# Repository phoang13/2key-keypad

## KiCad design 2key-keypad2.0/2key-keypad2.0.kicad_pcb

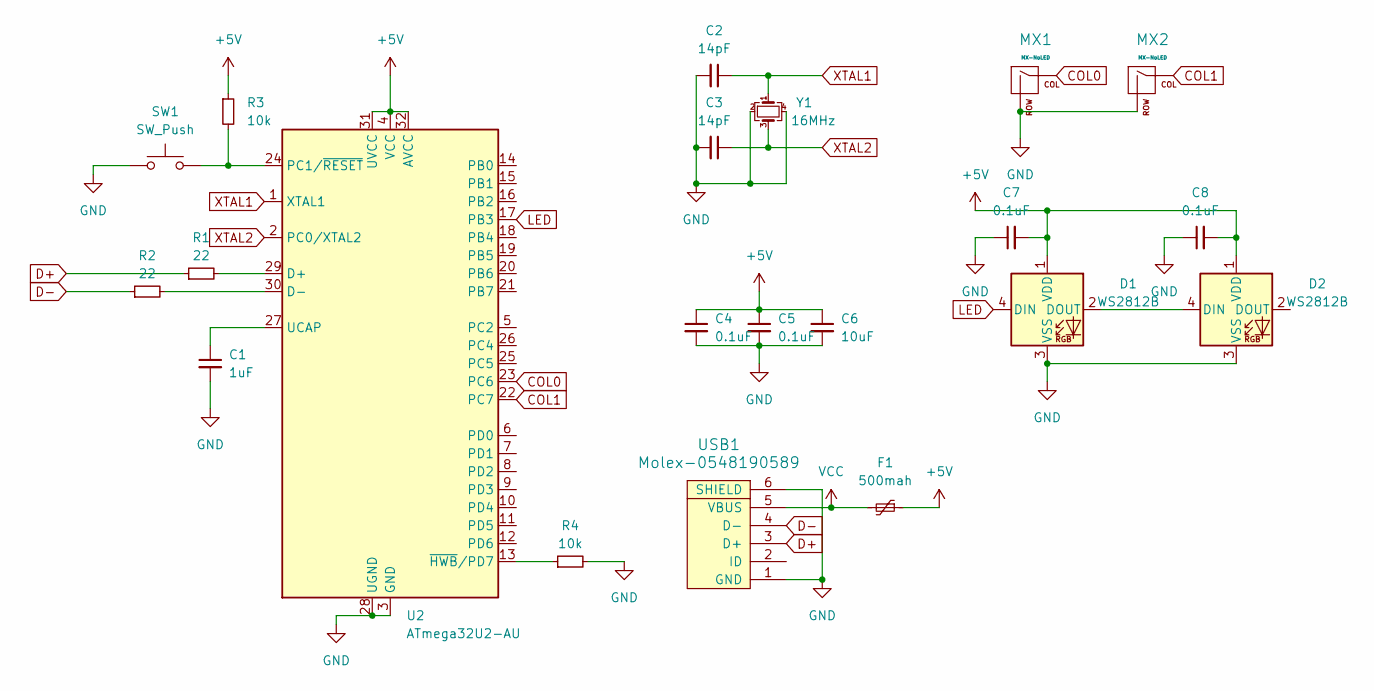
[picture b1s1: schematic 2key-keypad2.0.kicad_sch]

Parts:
C1: 1uF; C_0805_2012Metric_Pad1.18x1.45mm_HandSolder
C2, C3: 14pF; C_0805_2012Metric_Pad1.18x1.45mm_HandSolder
C4, C5, C7, C8: 0.1uF; C_0805_2012Metric_Pad1.18x1.45mm_HandSolder
C6: 10uF; C_0805_2012Metric_Pad1.18x1.45mm_HandSolder
D1, D2: WS2812B; LED_WS2812B_PLCC4_5.0x5.0mm_P3.2mm
F1: 500mah; Fuse_1206_3216Metric_Pad1.42x1.75mm_HandSolder
MX1, MX2: MX-NoLED; MXOnly-1U-Hotswap
R1, R2: 22; R_0805_2012Metric_Pad1.20x1.40mm_HandSolder
R3, R4: 10k; R_0805_2012Metric_Pad1.20x1.40mm_HandSolder
SW1: SW_Push; SKQGADE010
U2: ATmega32U2-AU; TQFP-32_7x7mm_P0.8mm
USB1: Molex-0548190589
Y1: 16MHz; Crystal_SMD_3225-4Pin_3.2x2.5mm_HandSoldering

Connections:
+5V: C4.1, C5.1, C6.1, C7.2, C8.2, D1.1 (VDD), D2.1 (VDD), F1.1, R3.1, U2.4 (VCC), U2.31 (UVCC), U2.32 (AVCC)
COL0: MX1.1 (COL), U2.23 (PC6)
COL1: MX2.1 (COL), U2.22 (PC7)
D+: R1.1, USB1.3 (D+)
D-: R2.1, USB1.4 (D-)
GND: C1.2, C2.2, C3.2, C4.2, C5.2, C6.2, C7.1, C8.1, D1.3 (VSS), D2.3 (VSS), MX1.2 (ROW), MX2.2 (ROW), R4.2, SW1.1, U2.3 (GND), U2.28 (UGND), USB1.1 (GND), USB1.6 (SHIELD), Y1.2, Y1.4
LED: D1.4 (DIN), U2.17 (PB3)
unnamed: D1.2 (DOUT), D2.4 (DIN)
unnamed: R1.2, U2.29 (D+)
unnamed: R2.2, U2.30 (D-)
unnamed: R3.2, SW1.2, U2.24 (PC1/~RESET)
unnamed: C1.1, U2.27 (UCAP)
unnamed: R4.1, U2.13 (~HWB/PD7)
VCC: F1.2, USB1.5 (VBUS)
XTAL1: C2.1, U2.1 (XTAL1), Y1.1
XTAL2: C3.1, U2.2 (PC0/XTAL2), Y1.3

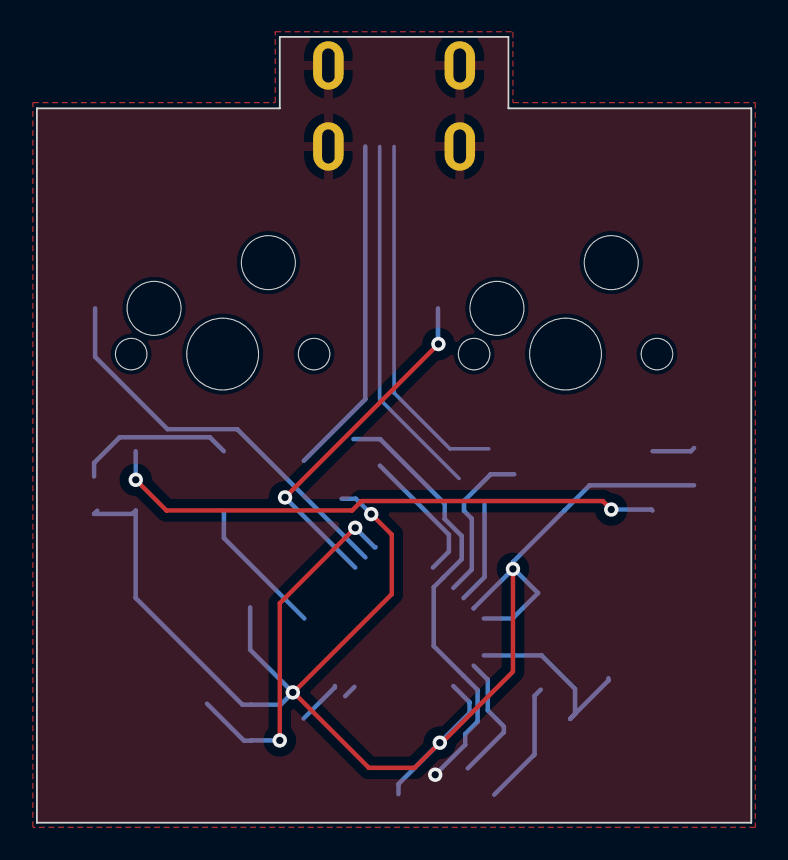
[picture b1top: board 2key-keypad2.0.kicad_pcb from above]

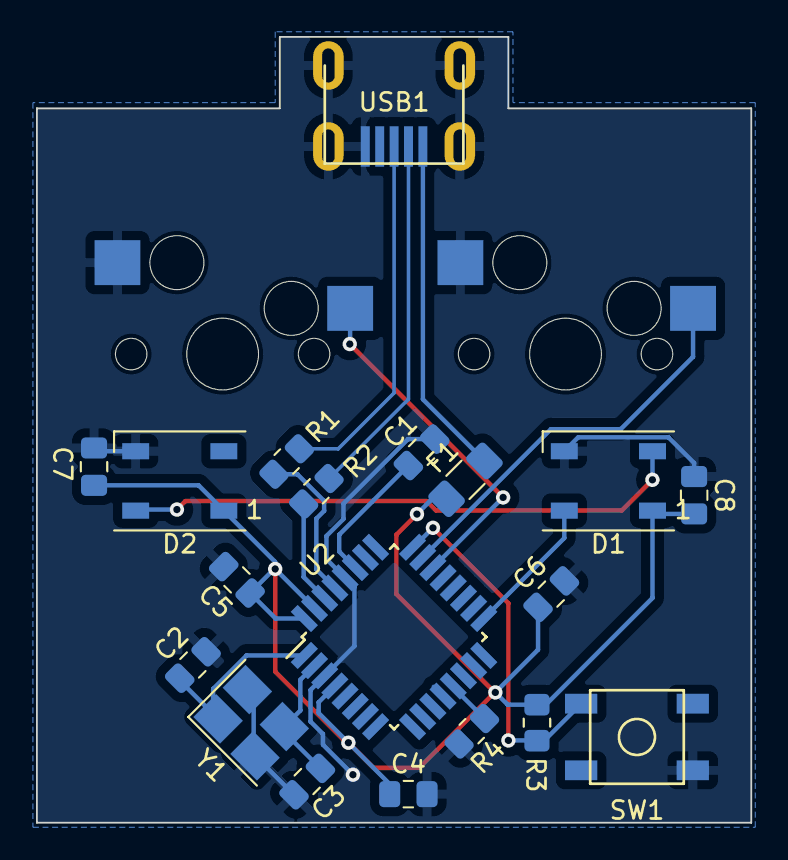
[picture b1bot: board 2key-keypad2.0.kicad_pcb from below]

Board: 2 copper layers, 39.7 x 43.7 mm, 21 parts (19 on the bottom side), 16 nets.

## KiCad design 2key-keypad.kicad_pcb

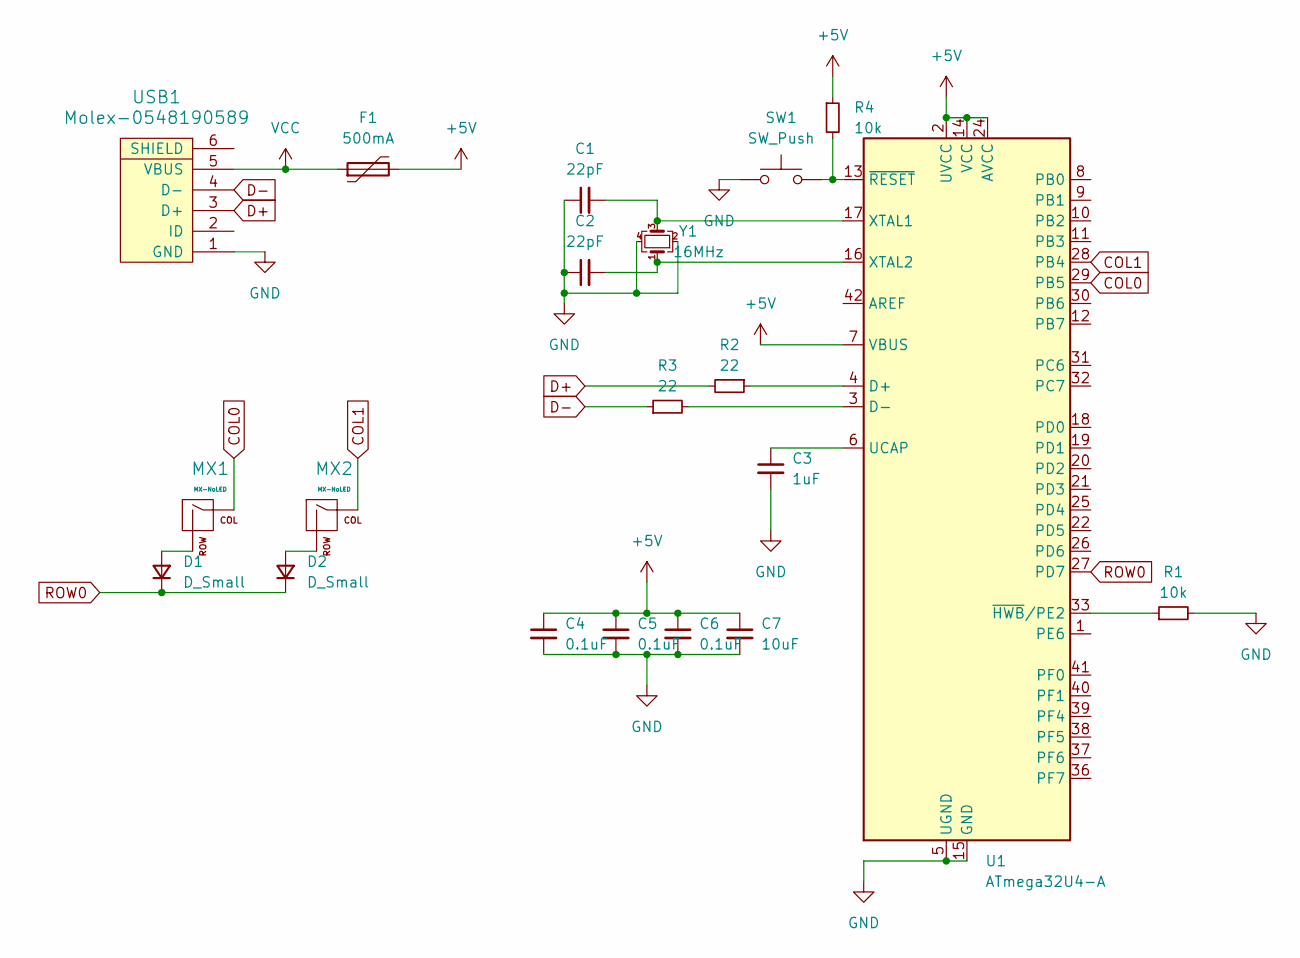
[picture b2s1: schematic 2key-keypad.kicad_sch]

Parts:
C1, C2: 22pF; C_0805_2012Metric
C3: 1uF; C_0805_2012Metric
C4, C5, C6: 0.1uF; C_0805_2012Metric
C7: 10uF; C_0805_2012Metric
D1, D2: D_Small; D_SOD-123
F1: 500mA; Fuse_1206_3216Metric
MX1, MX2: MX-NoLED; MXOnly-1U-Hotswap
R1, R4: 10k; R_0805_2012Metric
R2, R3: 22; R_0805_2012Metric
SW1: SW_Push; SKQG-1155865
U1: ATmega32U4-A; TQFP-44_10x10mm_P0.8mm
USB1: Molex-0548190589
Y1: 16MHz; Crystal_SMD_3225-4Pin_3.2x2.5mm

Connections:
+5V: C4.1, C5.1, C6.1, C7.1, F1.2, R4.1, U1.2 (UVCC), U1.7 (VBUS), U1.14 (VCC), U1.24 (AVCC), U1.34 (VCC), U1.44 (AVCC)
COL0: MX1.1 (COL), U1.29 (PB5)
COL1: MX2.1 (COL), U1.28 (PB4)
D+: R2.2, USB1.3 (D+)
D-: R3.1, USB1.4 (D-)
GND: C1.1, C2.1, C3.2, C4.2, C5.2, C6.2, C7.2, R1.2, SW1.1, U1.5 (UGND), U1.15 (GND), U1.23 (GND), U1.35 (GND), U1.43 (GND), USB1.1 (GND), Y1.2, Y1.4
unnamed: D1.2 (A), MX1.2 (ROW)
unnamed: D2.2 (A), MX2.2 (ROW)
unnamed: R2.1, U1.4 (D+)
unnamed: R3.2, U1.3 (D-)
unnamed: C3.1, U1.6 (UCAP)
unnamed: C1.2, U1.17 (XTAL1), Y1.3
unnamed: C2.2, U1.16 (XTAL2), Y1.1
unnamed: R1.1, U1.33 (~HWB/PE2)
unnamed: R4.2, SW1.2, U1.13 (~RESET)
ROW0: D1.1 (K), D2.1 (K), U1.27 (PD7)
VCC: F1.1, USB1.5 (VBUS)

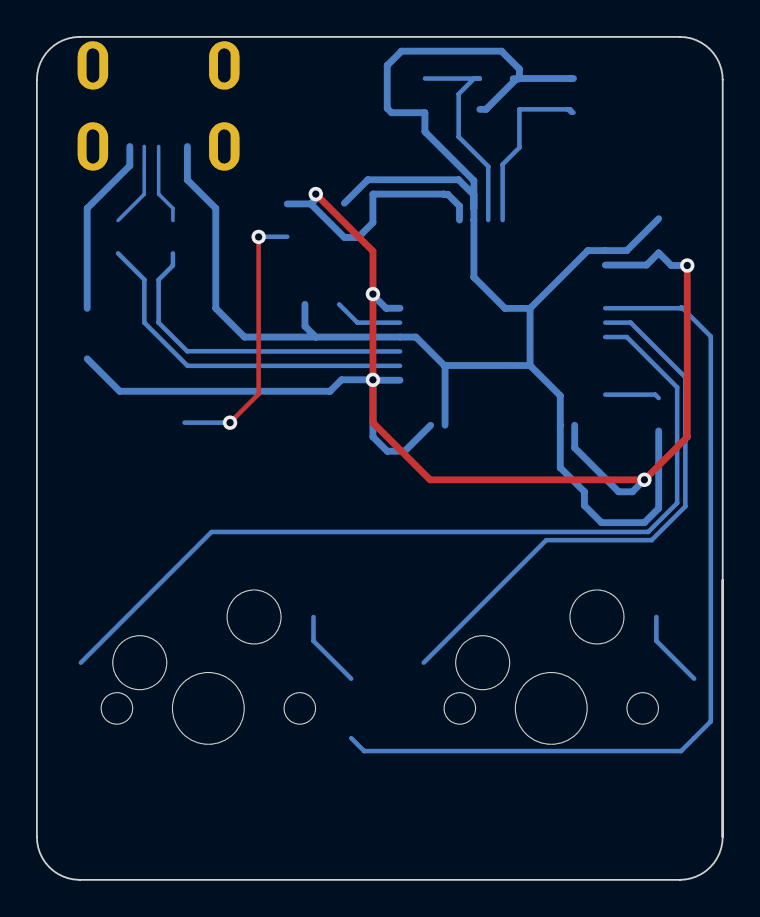
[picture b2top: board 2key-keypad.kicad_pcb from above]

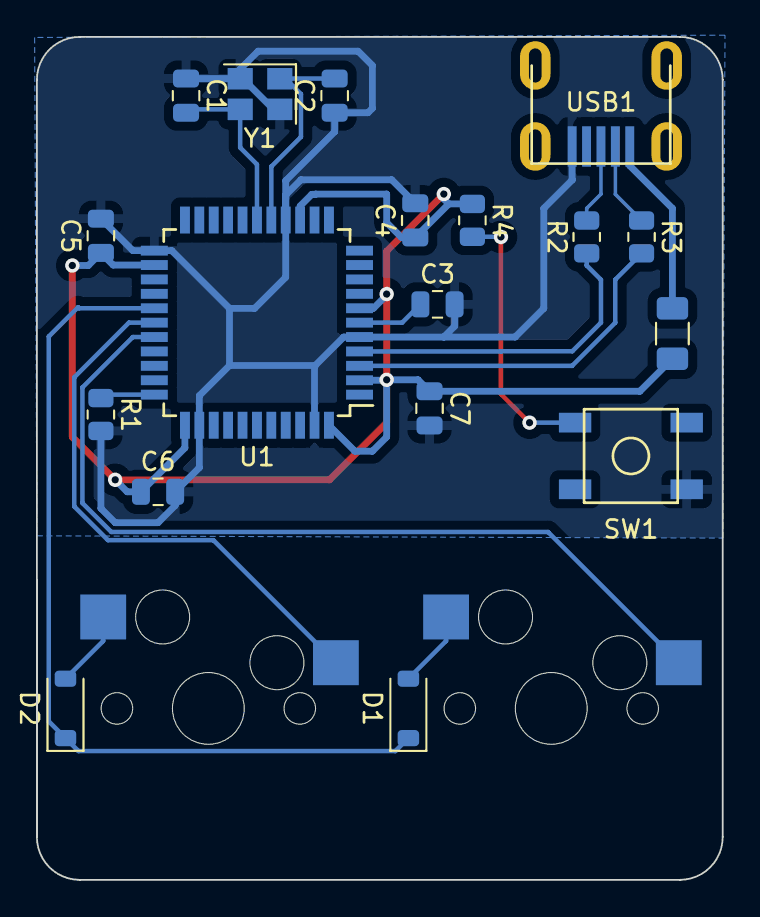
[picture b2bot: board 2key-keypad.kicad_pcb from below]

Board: 2 copper layers, 38.1 x 46.8 mm, 20 parts (18 on the bottom side), 17 nets.

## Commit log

2023-10-27 Created KiCad Project
2023-10-27 Opened Files
2023-10-27 Added Libraries
2023-10-27 Updated .gitignore
2023-10-27 Removed Ignore
2023-10-27 Add submodules
2023-10-27 Added footprint libraries
2023-10-27 Added Reference
2023-10-27 Completed Schematic for MCU
2023-10-28 Updated schematic
2023-10-29 Routed PCB - missing key matrix
2023-10-30 Finished First Schem
2023-10-31 Version 2.0
2023-10-31 V2.0
2023-11-02 Updated Schem
2023-11-02 Removed VIAs and equalized data traces
2023-11-16 Removed unnecessary
2023-11-16 Updated firmware
2023-11-16 Added VIA support
2023-11-17 Removed unnecessary lines of code
2023-11-17 Changed file name
2023-11-17 Removed
2023-11-17 Added RGB in VIA
2024-09-18 Final touches
2024-09-18 Cleaned up
2024-09-18 Added picture of the second pcb design
